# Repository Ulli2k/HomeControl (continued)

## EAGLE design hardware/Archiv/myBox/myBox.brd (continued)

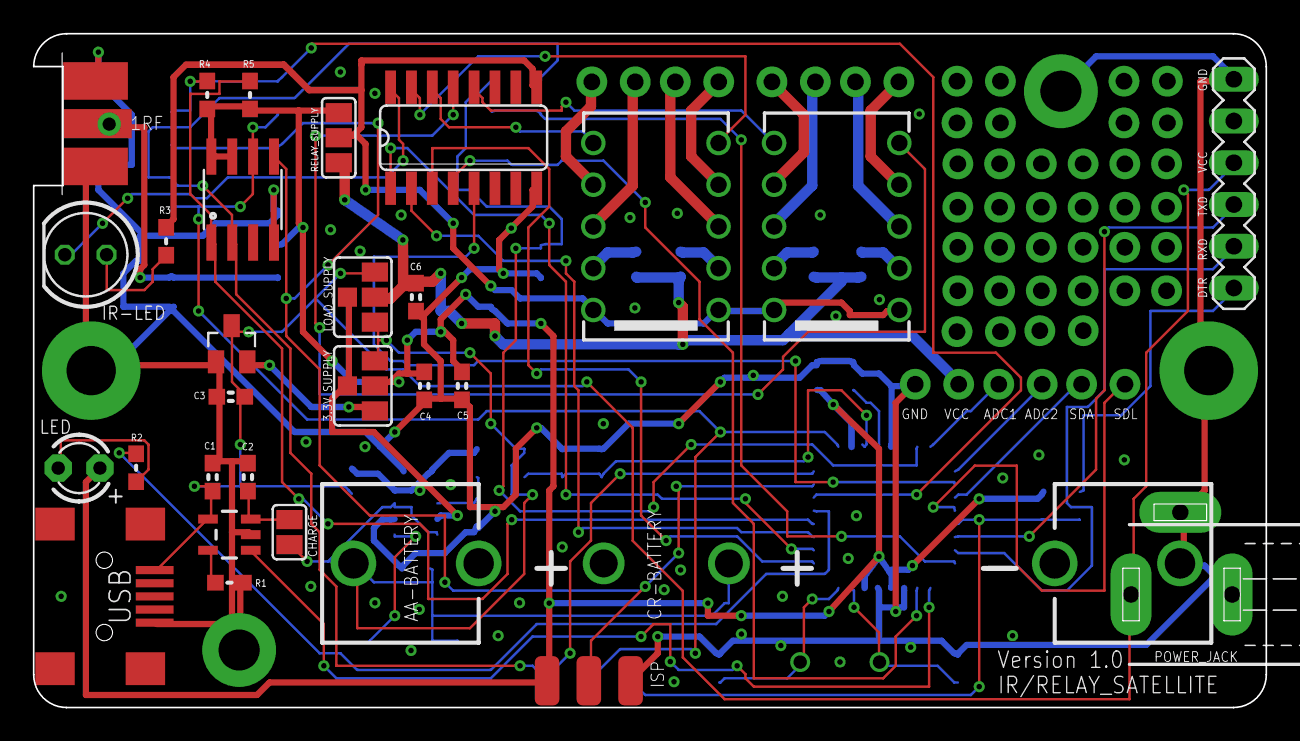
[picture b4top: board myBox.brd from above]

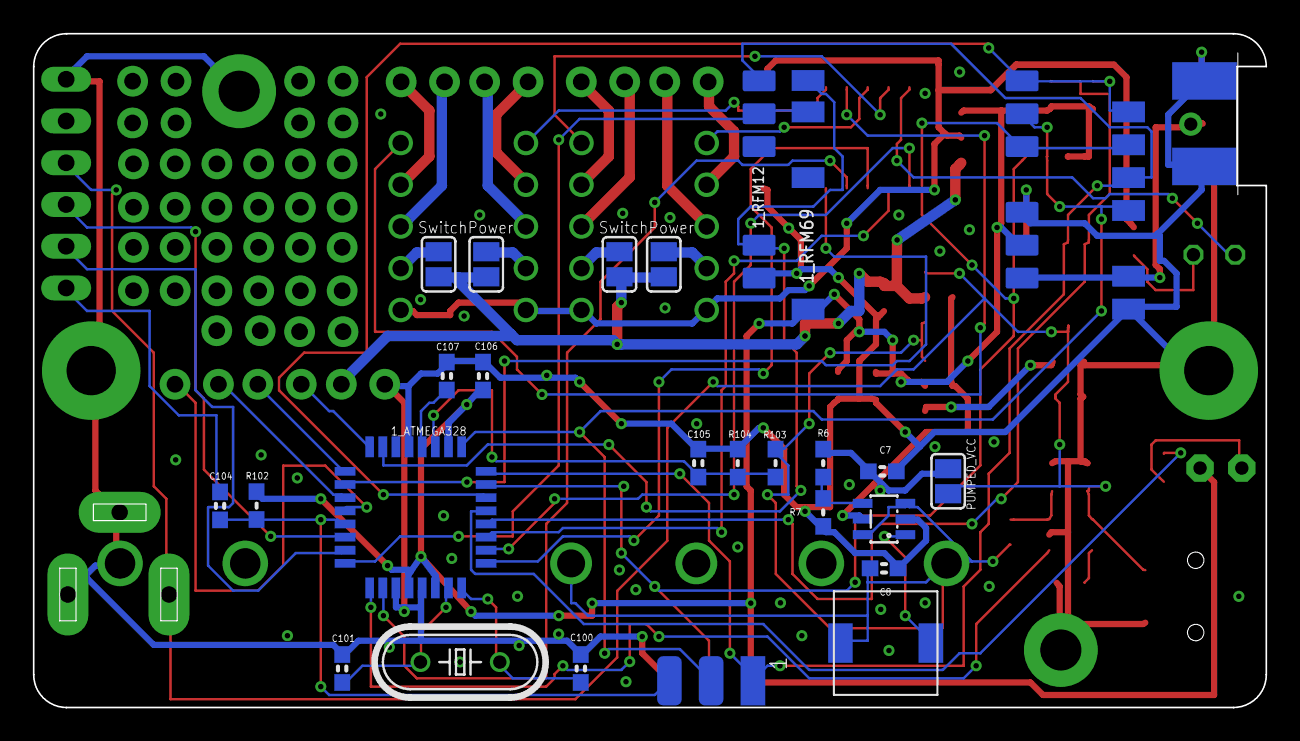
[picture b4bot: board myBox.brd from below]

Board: 2 copper layers, 75.0 x 41.0 mm, 81 parts (25 on the bottom side), 58 nets.

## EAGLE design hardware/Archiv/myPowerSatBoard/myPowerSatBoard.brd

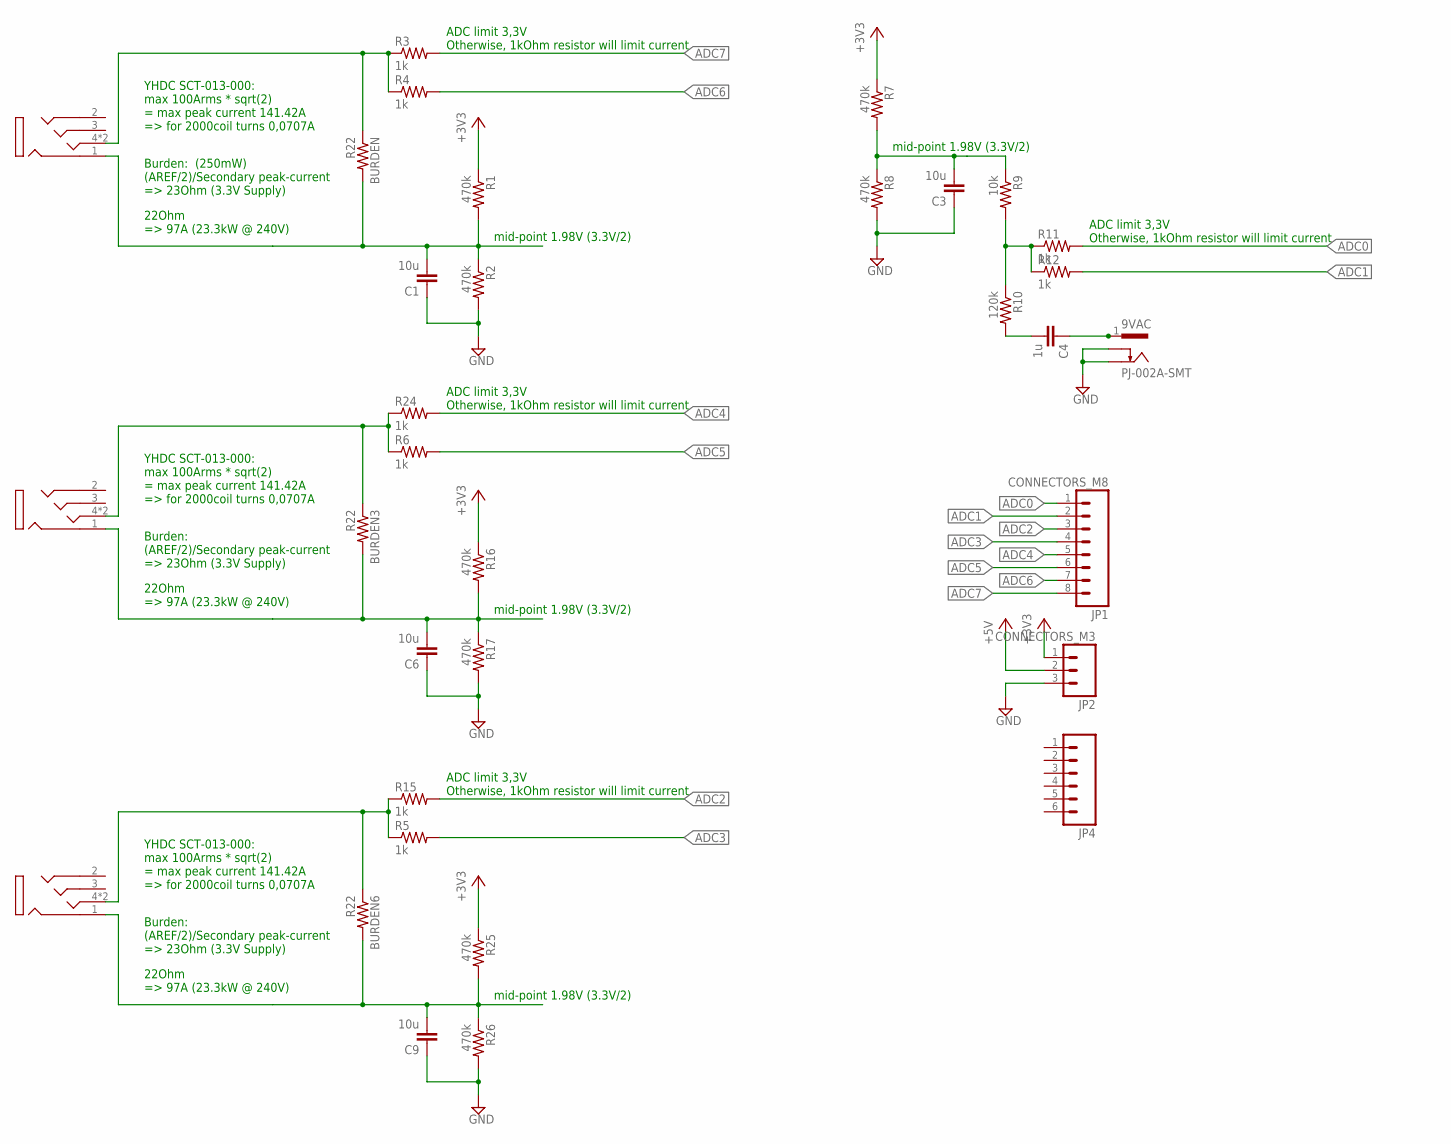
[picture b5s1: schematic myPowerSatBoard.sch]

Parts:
9VAC: PJ-002A-SMT; CUI_PJ-002B-SMT
BURDEN, BURDEN3, BURDEN6: R22; R0805
C1, C3, C6, C9: 10u; 0603-CAP
C4: 1u; 0603-CAP
CT1, CT4, CT7: 1503_13; 1503-03
JP1: CONNECTORS_M8; CONNECTORS_1X8
JP2: CONNECTORS_M3; CONNECTORS_1X3
JP4: CONNECTORS_M06SIP; CONNECTORS_1X06
R1, R2, R7, R8, R16, R17, R25, R26: 470k; 0603-RES
R3, R4, R5, R6, R11, R12, R15, R24: 1k; 0603-RES
R9: 10k; 0603-RES
R10: 120k; 0603-RES

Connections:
+3V3: JP2.1, R1.1, R7.1, R16.1, R25.1
+5V: JP2.2
ADC0: JP1.1, R11.2
ADC1: JP1.2, R12.2
ADC2: JP1.3, R15.2
ADC3: JP1.4, R5.2
ADC4: JP1.5, R24.2
ADC5: JP1.6, R6.2
ADC6: JP1.7, R4.2
ADC7: JP1.8, R3.2
GND: 9VAC.3, 9VAC.4, C1.1, C3.1, C6.1, C9.1, JP2.3, R2.2, R8.2, R17.2, R26.2
unnamed: BURDEN.2, C1.2, CT1.1, R1.2, R2.1
unnamed: BURDEN.1, CT1.4, CT1.4-2 (4), R3.1, R4.1
unnamed: C3.2, R7.2, R8.1, R9.1
unnamed: R9.2, R10.1, R11.1, R12.1
unnamed: C4.2, R10.2
unnamed: 9VAC.1, 9VAC.2, C4.1
unnamed: BURDEN3.2, C6.2, CT4.1, R16.2, R17.1
unnamed: BURDEN3.1, CT4.4, CT4.4-2 (4), R6.1, R24.1
unnamed: BURDEN6.2, C9.2, CT7.1, R25.2, R26.1
unnamed: BURDEN6.1, CT7.4, CT7.4-2 (4), R5.1, R15.1

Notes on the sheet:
mid-point 1.98V (3.3V/2)
ADC limit 3,3V Otherwise, 1kOhm resistor will limit current
YHDC SCT-013-000: max 100Arms * sqrt(2) = max peak current 141.42A => for 2000coil turns 0,0707A
Burden: (250mW) (AREF/2)/Secondary peak-current => 23Ohm (3.3V Supply)
22Ohm => 97A (23.3kW @ 240V)
Burden: (AREF/2)/Secondary peak-current => 23Ohm (3.3V Supply)

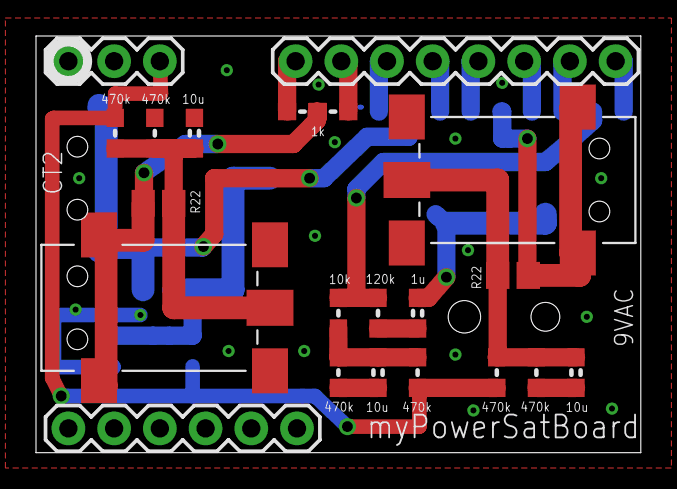
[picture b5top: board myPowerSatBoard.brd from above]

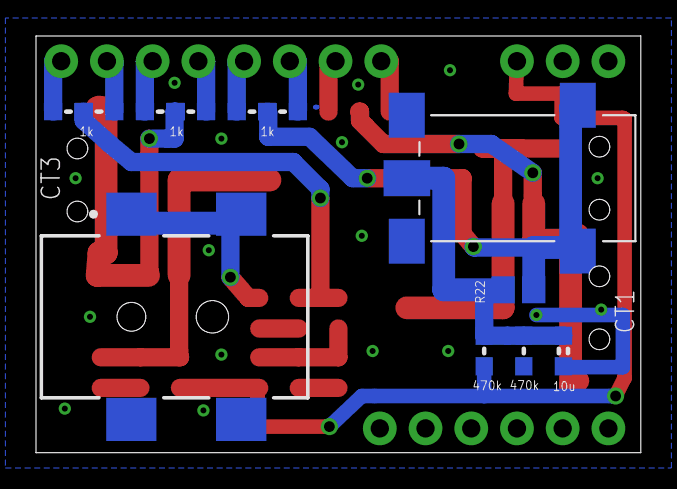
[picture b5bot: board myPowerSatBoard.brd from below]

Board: 2 copper layers, 33.6 x 23.1 mm, 33 parts (12 on the bottom side), 20 nets.

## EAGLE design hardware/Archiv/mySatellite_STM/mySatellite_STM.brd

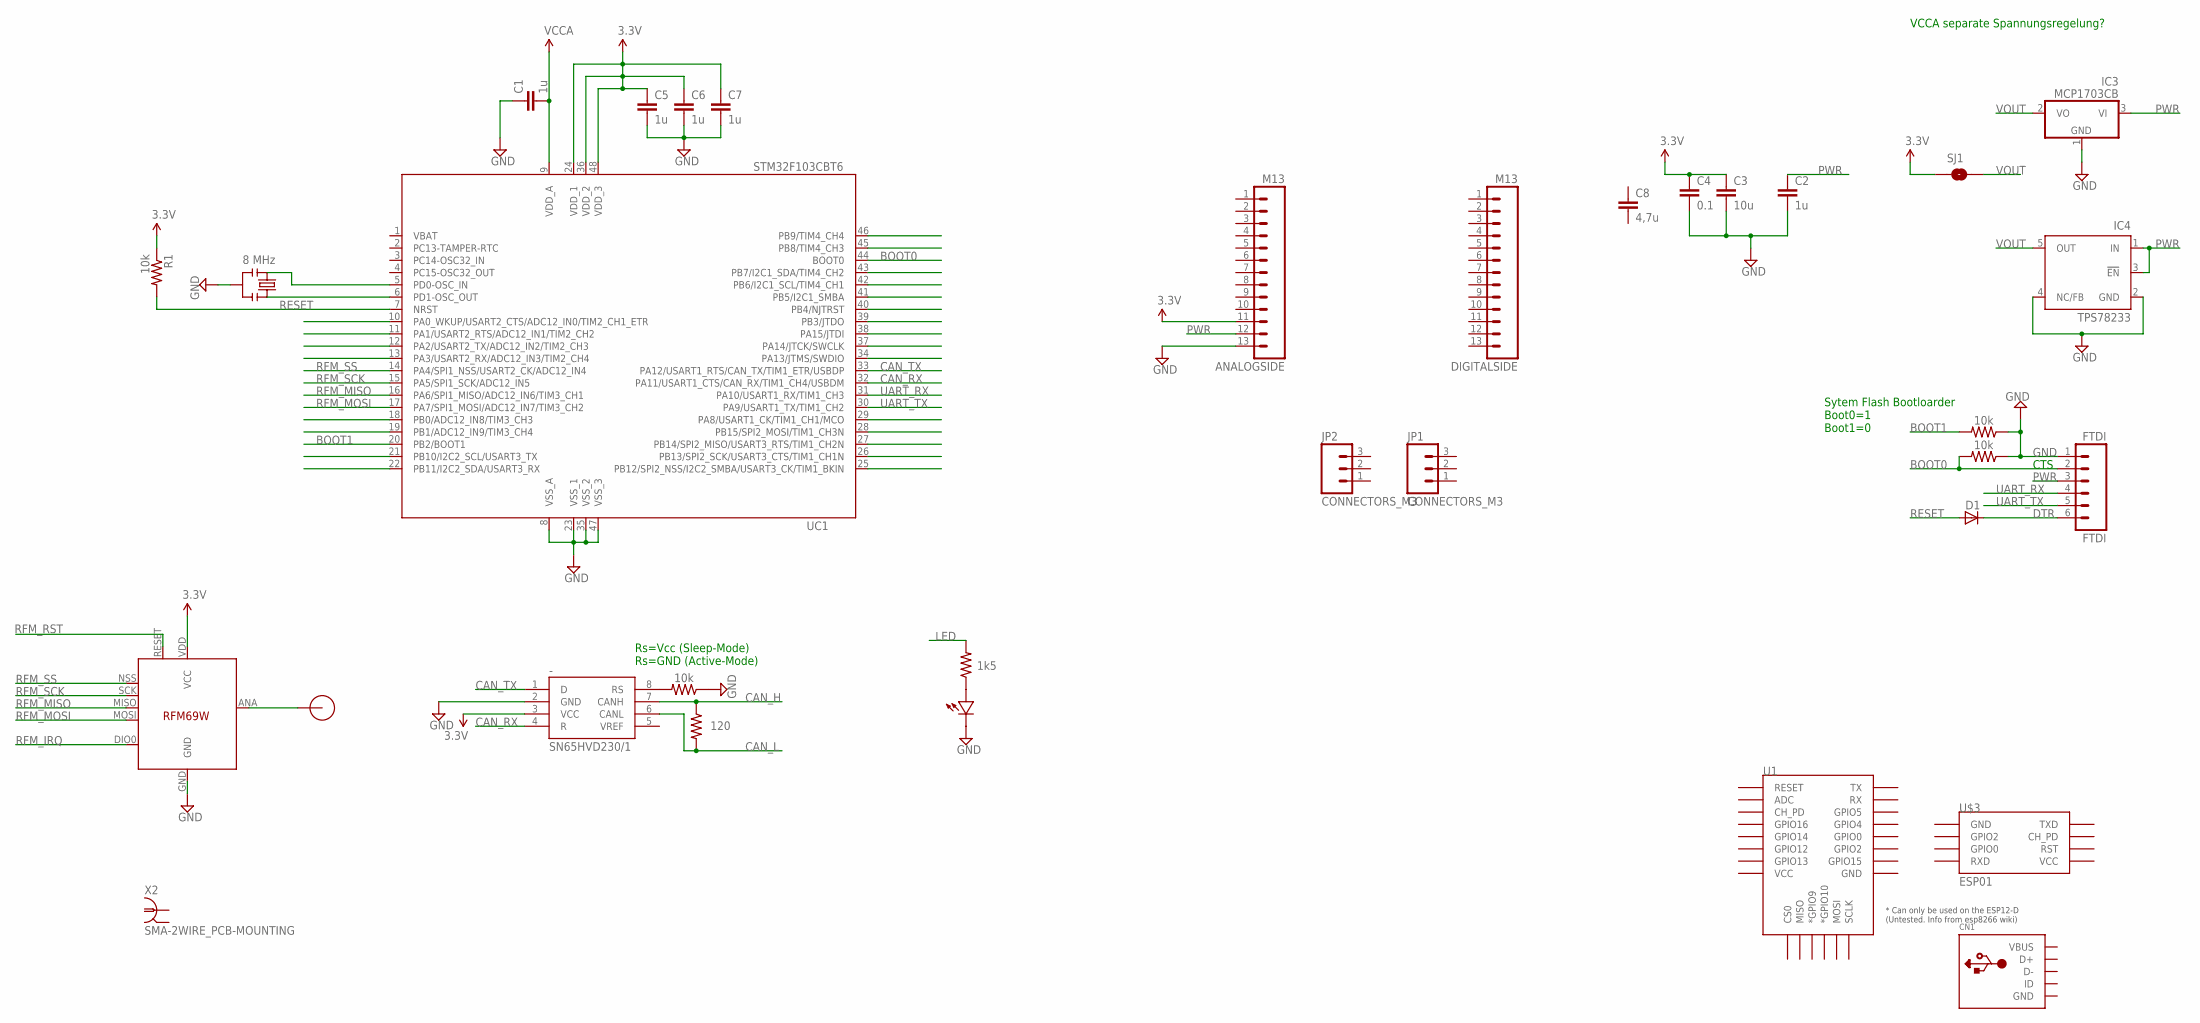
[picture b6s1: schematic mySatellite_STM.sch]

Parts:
-: SN65HVD230/1; SO8
ANALOGSIDE: M13; 1X13
C1, C2, C5, C6, C7: 1u; 0603-CAP
C3: 10u; 0805-CAP
C4: 0.1; 0603-CAP
C8: 4,7u; 0805-CAP
CN1: USBMINIB; USB-MINIB
D1: DIODE-SOD323-R; SOD323-R
DIGITALSIDE: M13; 1X13
FTDI: FTDI; 1X06
IC3: MCP1703CB; SOT23
IC4: TPS78233; SOT23-DBV
JP1, JP2: CONNECTORS_M3; CONNECTORS_1X3
R1, R3, R5, R7: 10k; 0603-RES
R2: 1k5; 0603-RES
R4: 120; 0603-RES
SJ1: SOLDERJUMPERTRACE; SJ_2S-TRACE
U1: ESP12ESMD; ESP12E-SMD
U$1: RFM12B_ANTENNA; RFM12B-ANTENNA
U$2: LED0603; 0603-LED
U$3: ESP01
U$5: RFM69_MINIPADS; RFM69W-MINPADS
UC1: STM32F103CBT6; LQFP48
X1: 8 MHz; RESONATOR-SMD
X2: SMA-2WIRE_PCB-MOUNTING; J01151A0931

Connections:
BOOT0: FTDI.2, R5.2, UC1.44 (BOOT0)
BOOT1: R7.2, UC1.20 (PB2/BOOT1)
CAN_H: -.7 (CANH), R4.1
CAN_L: -.6 (CANL), R4.2
CAN_RX: -.4 (R), UC1.32 (PA11/USART1_CTS/CAN_RX/TIM1_CH4/USBDM)
CAN_TX: -.1 (D), UC1.33 (PA12/USART1_RTS/CAN_TX/TIM1_ETR/USBDP)
DTR: D1.C, FTDI.6
GND: -.2 (GND), ANALOGSIDE.13, C1.1, C2.2, C3.2, C4.2, C5.2, C6.2, C7.2, CN1.GND, FTDI.1, IC3.1 (GND), IC4.2 (GND), IC4.4 (NC/FB), R3.1, R5.1, R7.1, U$2.MINUS, U$5.GND, UC1.8 (VSS_A), UC1.23 (VSS_1), UC1.35 (VSS_2), UC1.47 (VSS_3), X1.2
LED: R2.2
unnamed: R2.1, U$2.PLUS
unnamed: U$1.P$1, U$5.ANA (ANT)
unnamed: C1.2, UC1.9 (VDD_A)
unnamed: UC1.5 (PD0-OSC_IN), X1.1
unnamed: -.8 (RS), R3.2
unnamed: UC1.6 (PD1-OSC_OUT), X1.3
PWR: ANALOGSIDE.12, C2.1, FTDI.3, IC3.3 (VI), IC4.1 (IN), IC4.3 (!EN)
RESET: D1.A, R1.2, UC1.7 (NRST)
RFM_IRQ: U$5.DIO0 (DIO0/IRQ)
RFM_MISO: U$5.MISO, UC1.16 (PA6/SPI1_MISO/ADC12_IN6/TIM3_CH1)
RFM_MOSI: U$5.MOSI, UC1.17 (PA7/SPI1_MOSI/ADC12_IN7/TIM3_CH2)
RFM_RST: U$5.RESET
RFM_SCK: U$5.SCK, UC1.15 (PA5/SPI1_SCK/ADC12_IN5)
RFM_SS: U$5.NSS (SEL), UC1.14 (PA4/SPI1_NSS/USART2_CK/ADC12_IN4)
UART_RX: FTDI.4, UC1.31 (PA10/USART1_RX/TIM1_CH3)
UART_TX: FTDI.5, UC1.30 (PA9/USART1_TX/TIM1_CH2)
VBAT: UC1.1 (VBAT)
VBUS: CN1.VBUS
VCC: -.3 (VCC), ANALOGSIDE.11, C3.1, C4.1, C5.1, C6.1, C7.1, R1.1, SJ1.1, U$5.VDD (VCC), UC1.24 (VDD_1), UC1.36 (VDD_2), UC1.48 (VDD_3)
VOUT: IC3.2 (VO), IC4.5 (OUT), SJ1.2

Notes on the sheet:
Rs=Vcc (Sleep-Mode) Rs=GND (Active-Mode)
CTS
Sytem Flash Bootloarder Boot0=1 Boot1=0
VCCA separate Spannungsregelung?

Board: 2 copper layers, 33 parts (3 on the bottom side), 24 nets, no tracks yet.

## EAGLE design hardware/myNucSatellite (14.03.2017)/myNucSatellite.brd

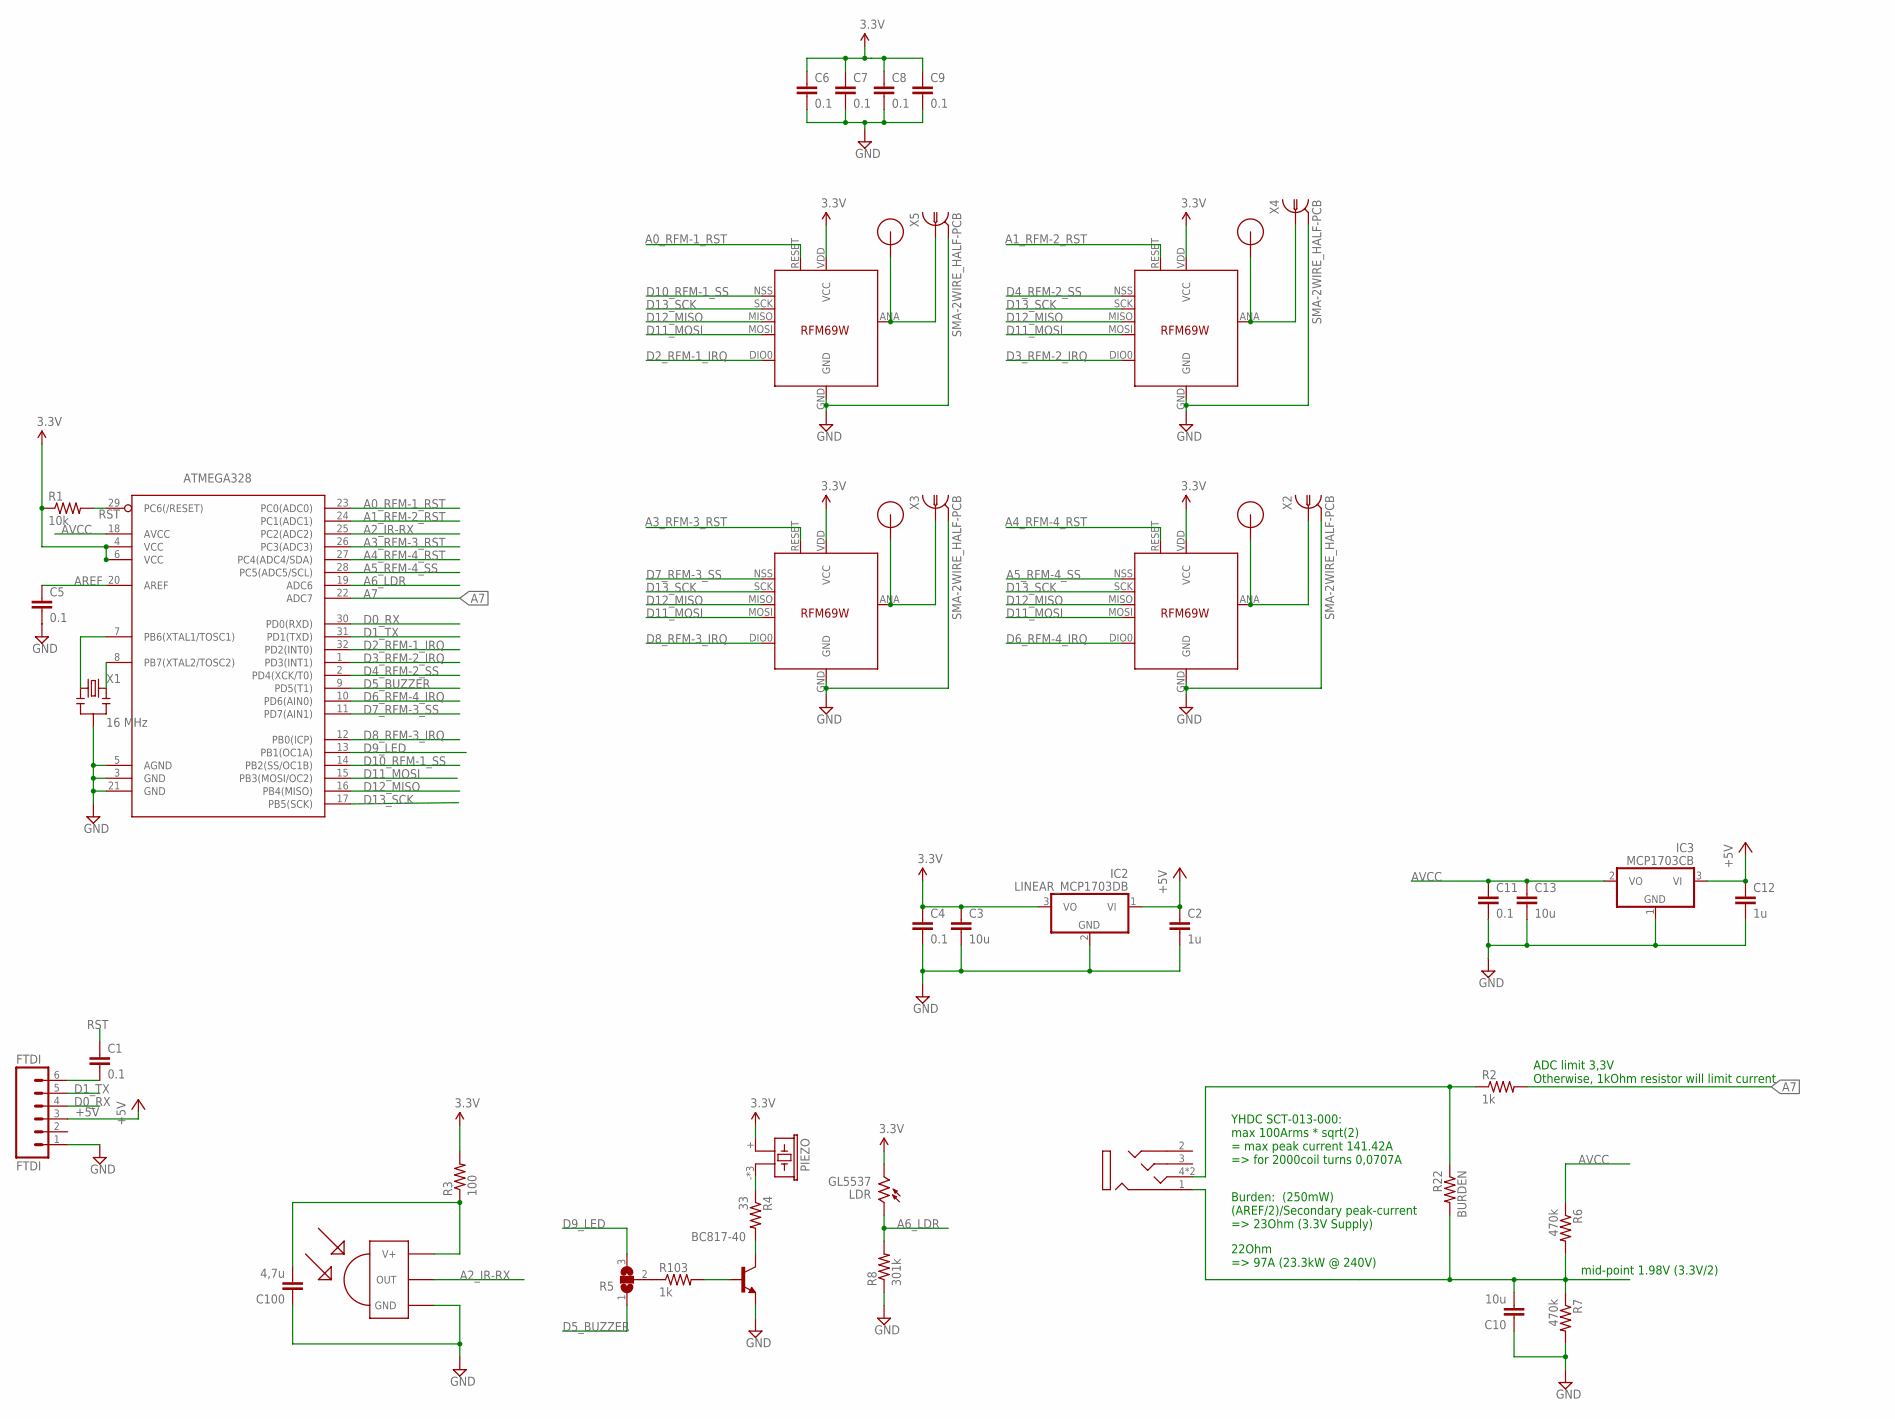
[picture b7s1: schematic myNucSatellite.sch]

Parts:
ATMEGA328: ATMega-328; TQFP32-08
BC817-40: BC817-40-NPN-SOT23-BEC; SOT23-BEC
BURDEN: R22; R0805
C1, C4, C5, C6, C7, C8, C9, C11: 0.1; 0603-CAP
C2, C12: 1u; 0603-CAP
C3, C13: 10u; 0805-CAP
C10: 10u; 0603-CAP
C100: 4,7u; 0603-CAP
CT1: 1503_13; 1503-03
FTDI: FTDI; 1X06
IC2: LINEAR_MCP1703DB; LINEAR_SOT223
IC3: MCP1703CB; SOT23
IR-RX: TSOP4836; TSOP18XX
LDR: GL5537; M9960
PIEZO: BUZZER-PIEZO_SMD
R1: 10k; 0603-RES
R2, R103: 1k; 0603-RES
R3: 100; 0603-RES
R4: 33; 0603-RES
R5: SELECT0603-SELECT; 0603-SELECT
R6, R7: 470k; 0603-RES
R8: 301k; 0603-RES
U$3, U$6, U$8, U$10: RFM12B_ANTENNA; RFM12B-ANTENNA
U$4, U$7, U$9, U$11: RFM69_MINIPADS; RFM69W-MINPADS
X1: 16 MHz; RESONATOR-SMD
X2, X3, X4, X5: SMA-2WIRE_HALF-PCB; SMA-EDGE-HALF

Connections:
+5V: C2.1, C12.1, FTDI.3, IC2.1 (VI), IC3.3 (VI)
A0_RFM-1_RST: ATMEGA328.23 (PC0(ADC0)), U$4.RESET
A1_RFM-2_RST: ATMEGA328.24 (PC1(ADC1)), U$7.RESET
A2_IR-RX: ATMEGA328.25 (PC2(ADC2)), IR-RX.OUT
A3_RFM-3_RST: ATMEGA328.26 (PC3(ADC3)), U$9.RESET
A4_RFM-4_RST: ATMEGA328.27 (PC4(ADC4/SDA)), U$11.RESET
A5_RFM-4_SS: ATMEGA328.28 (PC5(ADC5/SCL)), U$11.NSS (SEL)
A6_LDR: ATMEGA328.19 (ADC6), LDR.1, R8.2
A7: ATMEGA328.22 (ADC7), R2.2
AREF: ATMEGA328.20 (AREF), C5.1
AVCC: ATMEGA328.18 (AVCC), C11.1, C13.1, IC3.2 (VO), R6.1
D0_RX: ATMEGA328.30 (PD0(RXD)), FTDI.4
D1_TX: ATMEGA328.31 (PD1(TXD)), FTDI.5
D2_RFM-1_IRQ: ATMEGA328.32 (PD2(INT0)), U$4.DIO0 (DIO0/IRQ)
D3_RFM-2_IRQ: ATMEGA328.1 (PD3(INT1)), U$7.DIO0 (DIO0/IRQ)
D4_RFM-2_SS: ATMEGA328.2 (PD4(XCK/T0)), U$7.NSS (SEL)
D5_BUZZER: ATMEGA328.9 (PD5(T1)), R5.1
D6_RFM-4_IRQ: ATMEGA328.10 (PD6(AIN0)), U$11.DIO0 (DIO0/IRQ)
D7_RFM-3_SS: ATMEGA328.11 (PD7(AIN1)), U$9.NSS (SEL)
D8_RFM-3_IRQ: ATMEGA328.12 (PB0(ICP)), U$9.DIO0 (DIO0/IRQ)
D9_LED: ATMEGA328.13 (PB1(OC1A)), R5.3
D10_RFM-1_SS: ATMEGA328.14 (PB2(SS/OC1B)), U$4.NSS (SEL)
D11_MOSI: ATMEGA328.15 (PB3(MOSI/OC2)), U$4.MOSI, U$7.MOSI, U$9.MOSI, U$11.MOSI
D12_MISO: ATMEGA328.16 (PB4(MISO)), U$4.MISO, U$7.MISO, U$9.MISO, U$11.MISO
D13_SCK: ATMEGA328.17 (PB5(SCK)), U$4.SCK, U$7.SCK, U$9.SCK, U$11.SCK
GND: ATMEGA328.3 (GND), ATMEGA328.5 (AGND), ATMEGA328.21 (GND), BC817-40.E, C2.2, C3.2, C4.2, C5.2, C6.2, C7.2, C8.2, C9.2, C10.1, C11.2, C12.2, C13.2, C100.1, FTDI.1, IC2.2 (GND), IC3.1 (GND), IR-RX.GND, R7.2, R8.1, U$4.GND, U$7.GND, U$9.GND, U$11.GND, X1.2, X2.GND@0 (GND), X2.GND@1 (GND), X3.GND@0 (GND), X3.GND@1 (GND), X4.GND@0 (GND), X4.GND@1 (GND), X5.GND@0 (GND), X5.GND@1 (GND)
unnamed: ATMEGA328.7 (PB6(XTAL1/TOSC1)), X1.1
unnamed: BURDEN.2, C10.2, CT1.1, R6.2, R7.1
unnamed: PIEZO.- (2), PIEZO.DUMMY (2), PIEZO.DUMMY1 (2), R4.1
unnamed: R5.2, R103.1
unnamed: U$3.P$1, U$4.ANA (ANT), X5.SIG (SIGNAL)
unnamed: BURDEN.1, CT1.4, CT1.4-2 (4), R2.1
unnamed: U$6.P$1, U$7.ANA (ANT), X4.SIG (SIGNAL)
unnamed: BC817-40.C, R4.2
unnamed: U$8.P$1, U$9.ANA (ANT), X3.SIG (SIGNAL)
unnamed: U$10.P$1, U$11.ANA (ANT), X2.SIG (SIGNAL)
unnamed: BC817-40.B, R103.2
unnamed: C100.2, IR-RX.VCC (V+), R3.1
unnamed: C1.2, FTDI.6
unnamed: ATMEGA328.8 (PB7(XTAL2/TOSC2)), X1.3
RST: ATMEGA328.29 (PC6(/RESET)), C1.1, R1.2
VCC: ATMEGA328.4 (VCC), ATMEGA328.6 (VCC), C3.1, C4.1, C6.1, C7.1, C8.1, C9.1, IC2.3 (VO), LDR.2, PIEZO.+ (1), R1.1, R3.2, U$4.VDD (VCC), U$7.VDD (VCC), U$9.VDD (VCC), U$11.VDD (VCC)

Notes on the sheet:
mid-point 1.98V (3.3V/2)
ADC limit 3,3V Otherwise, 1kOhm resistor will limit current
YHDC SCT-013-000: max 100Arms * sqrt(2) = max peak current 141.42A => for 2000coil turns 0,0707A
Burden: (250mW) (AREF/2)/Secondary peak-current => 23Ohm (3.3V Supply)
22Ohm => 97A (23.3kW @ 240V)

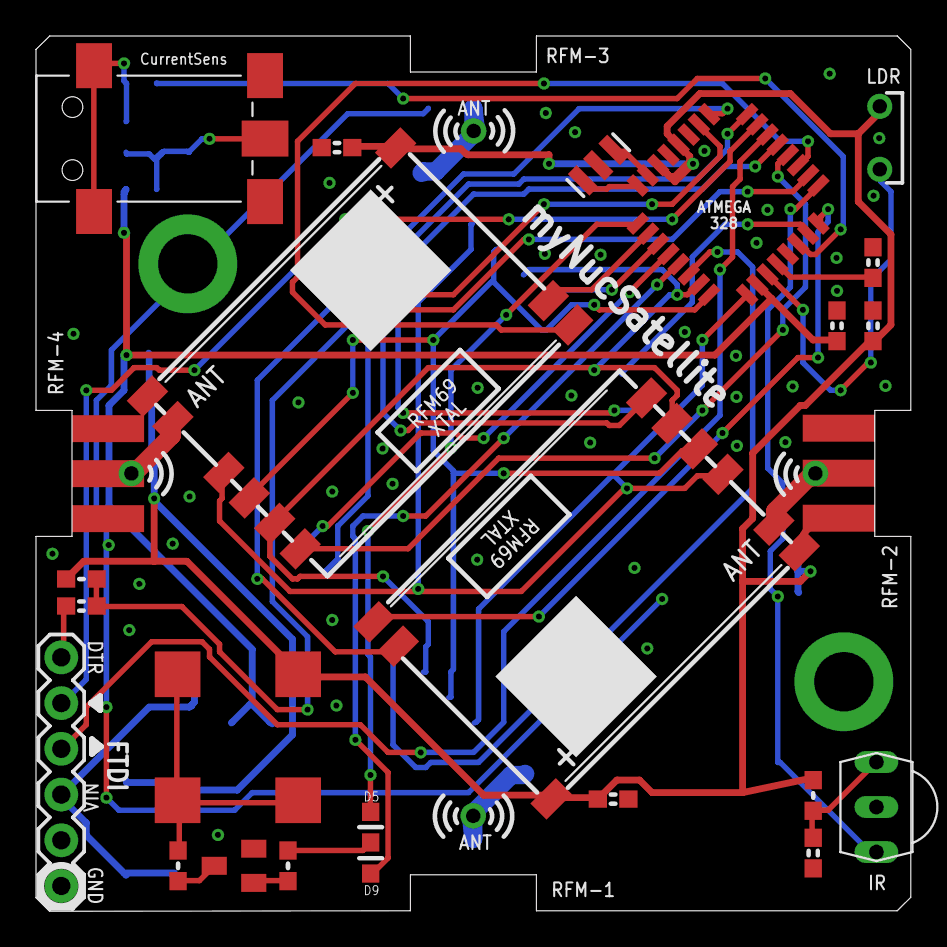
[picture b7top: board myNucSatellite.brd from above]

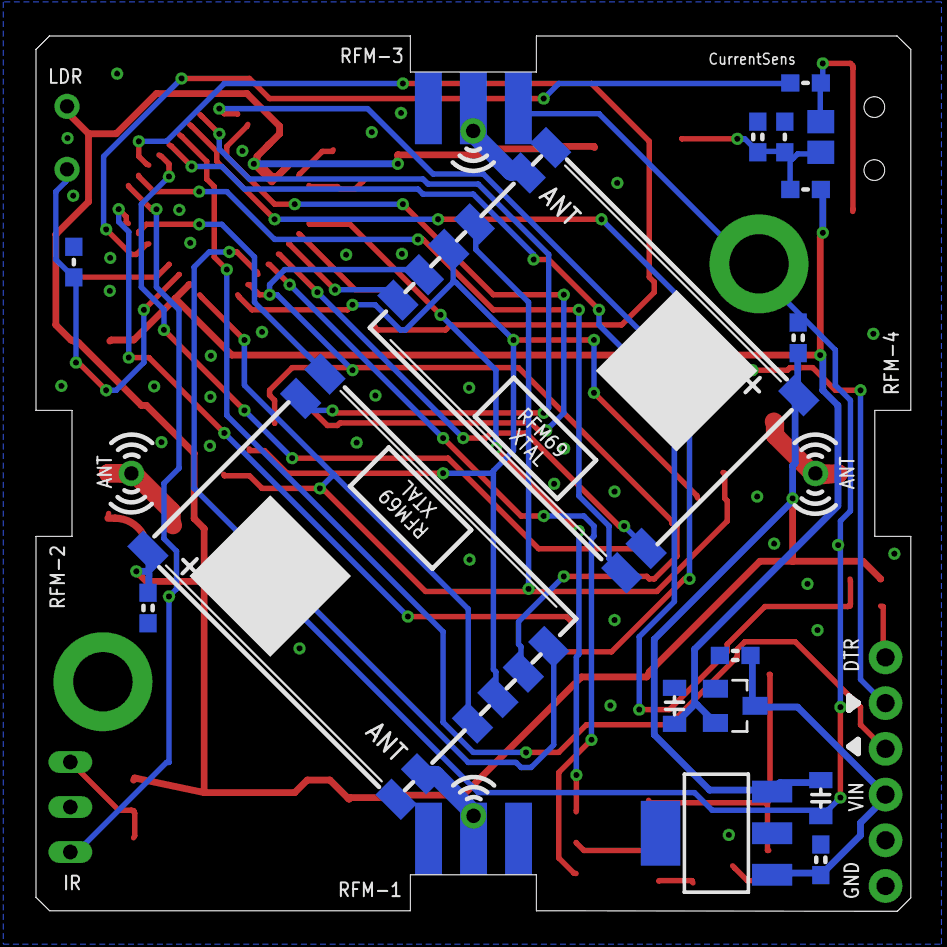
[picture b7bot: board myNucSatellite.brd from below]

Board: 2 copper layers, 48.6 x 48.6 mm, 46 parts (18 on the bottom side), 42 nets.
